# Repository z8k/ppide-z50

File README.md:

# ppide-z50
PPIDE card for Z50Bus

Heavily based on https://github.com/electrified/rc2014-82c55-ide

Intended for use with a horizontal-mounting 44-pin IDE Disk-On-Module module, this card omits the 40-pin IDE connector and external power input jack.

Notes:
1. Address selection is with the jumper pins in the lower right. Address bits A1 and A0 are ignored. Set to 0x20 (one jumper, on pin A5) for use with RomWBW and/or Fuzix.
2. You may wish to lower the value of R101 or use a super-bright LED if the disk activity light is a bit dim.

| Reference |  Value |
|-----------|--------|
| R101 | 470R resistor or lower value suitable for your LED |
| R102 | 10K resistor |
| R103 | 10K resistor |
| R104 | 10K resistor |
| C101 | 0.1uF ceramic capacitor |
| C102 | 0.1uF ceramic capacitor |
| C103 | 0.1uF ceramic capacitor |
| RN101 | 10K SIP resistor (8 pins, 7 resistors) |
| D101 | LED |
| U101 | 74HCT688 |
| U102 | 74HCT04 |
| U103 | 82C55A (PLCC package) |
| J101 | 2x25 2.54mm right-angle male box header |
| J102 | 2x8 2.54mm pitch right-angle pin header |
| J103 | 2x22 2mm pitch pin header |

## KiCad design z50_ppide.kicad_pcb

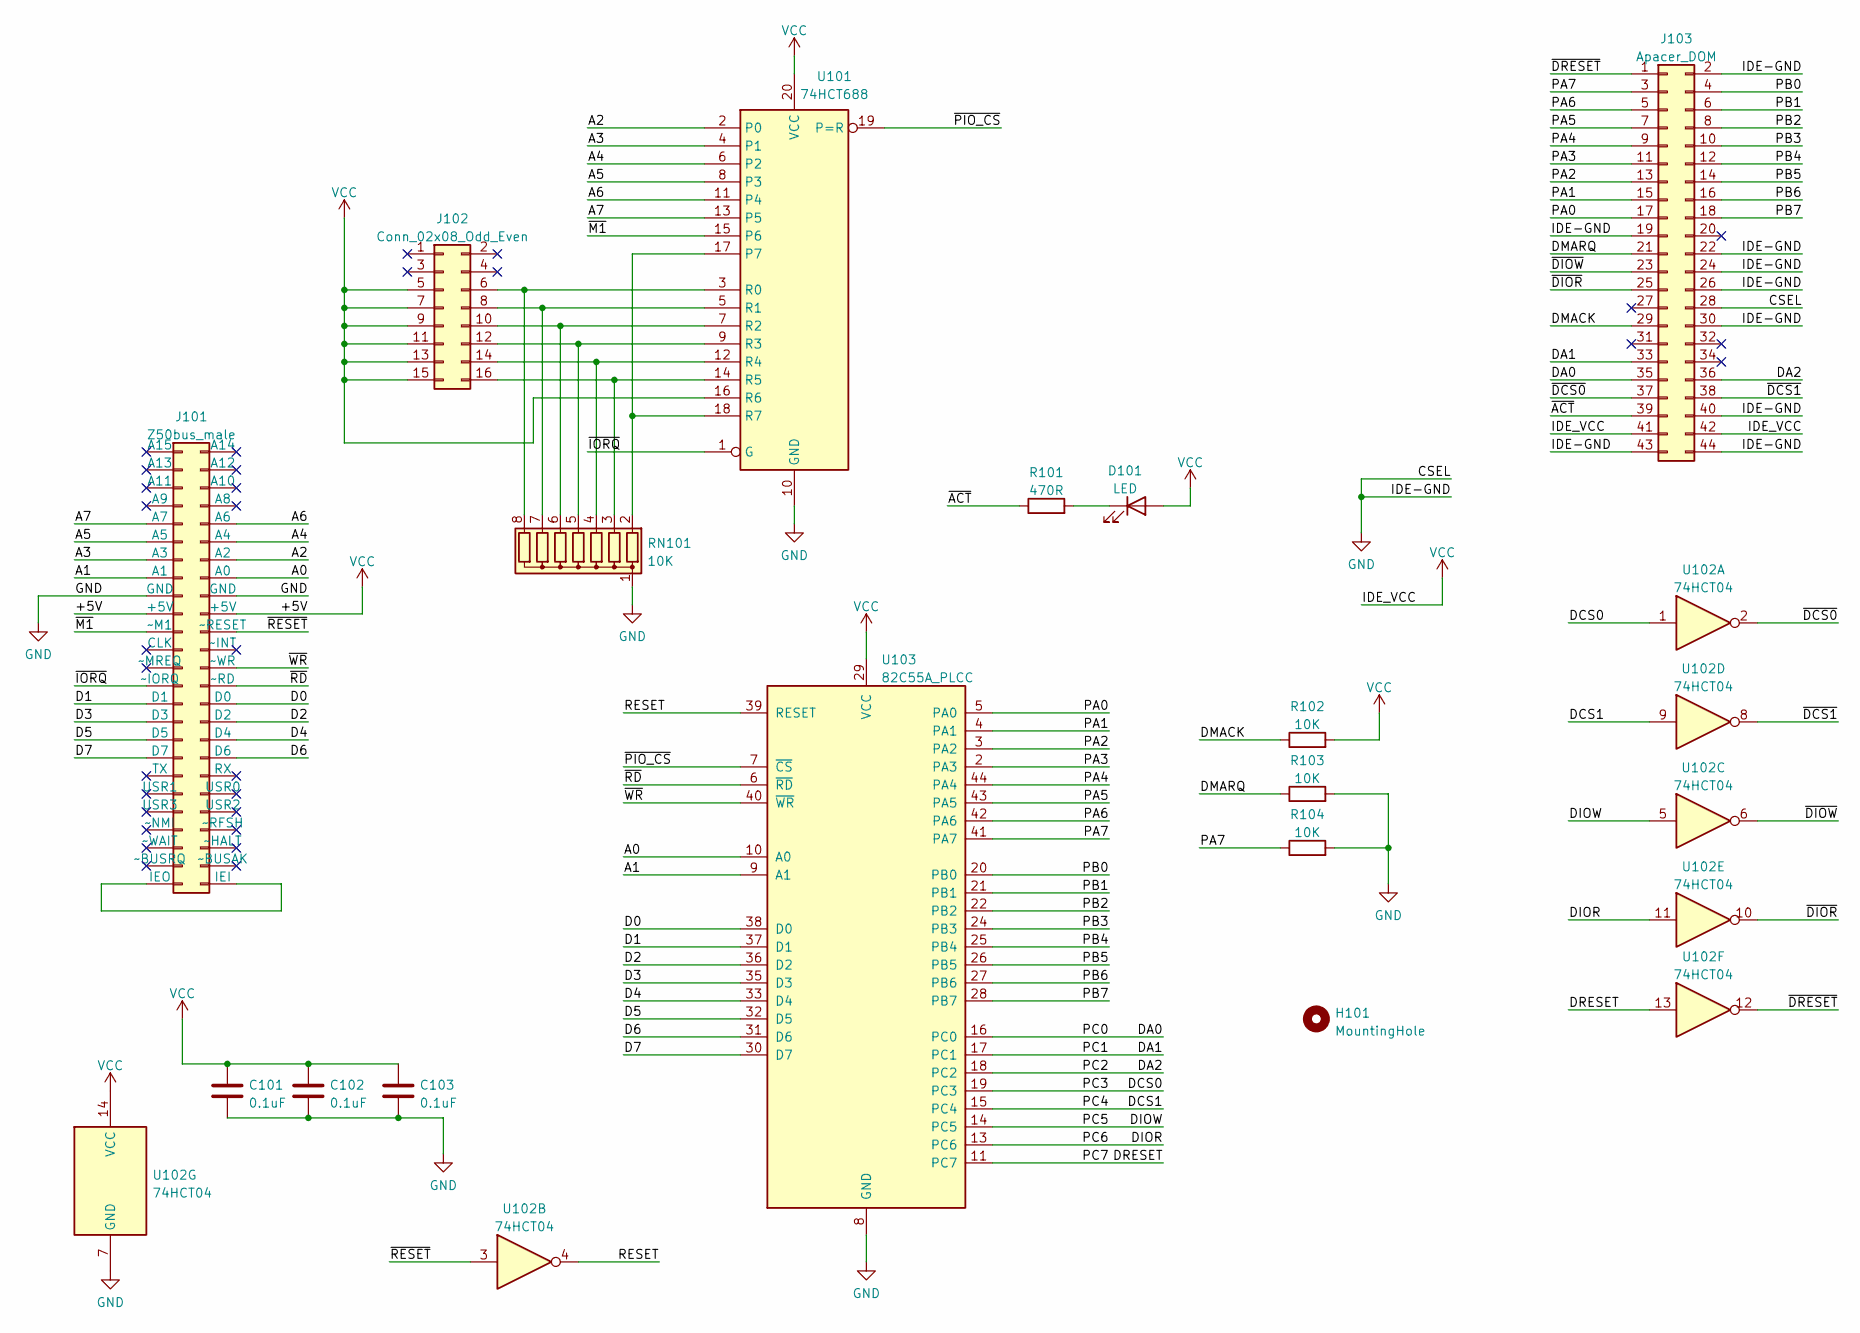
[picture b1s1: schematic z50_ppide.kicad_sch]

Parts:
C101, C102, C103: 0.1uF; C_Disc_D3.8mm_W2.6mm_P2.50mm
D101: LED; LED_D3.0mm
H101: MountingHole; MountingHole_3.2mm_M3_DIN965_Pad_TopBottom
J101: Z50bus_male; Z50bus module card edge
J102: Conn_02x08_Odd_Even; PinHeader_2x08_P2.54mm_Horizontal
J103: Apacer_DOM; Apacer DOM
R101: 470R; R_Axial_DIN0207_L6.3mm_D2.5mm_P10.16mm_Horizontal
R102, R103, R104: 10K; R_Axial_DIN0207_L6.3mm_D2.5mm_P10.16mm_Horizontal
RN101: 10K; R_Array_SIP8
U101: 74HCT688; DIP-20_W7.62mm_LongPads
U102: 74HCT04; DIP-14_W7.62mm_LongPads
U103: 82C55A_PLCC; PLCC-44_THT-Socket

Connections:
/A0: J101.16 (A0), U103.10 (A0)
/A1: J101.15 (A1), U103.9 (A1)
/A2: J101.14 (A2), U101.2 (P0)
/A3: J101.13 (A3), U101.4 (P1)
/A4: J101.12 (A4), U101.6 (P2)
/A5: J101.11 (A5), U101.8 (P3)
/A6: J101.10 (A6), U101.11 (P4)
/A7: J101.9 (A7), U101.13 (P5)
/D0: J101.30 (D0), U103.38 (D0)
/D1: J101.29 (D1), U103.37 (D1)
/D2: J101.32 (D2), U103.36 (D2)
/D3: J101.31 (D3), U103.35 (D3)
/D4: J101.34 (D4), U103.33 (D4)
/D5: J101.33 (D5), U103.32 (D5)
/D6: J101.36 (D6), U103.31 (D6)
/D7: J101.35 (D7), U103.30 (D7)
/DA0: J103.35, U103.16 (PC0)
/DA1: J103.33, U103.17 (PC1)
/DA2: J103.36, U103.18 (PC2)
/DCS0: U102.1, U103.19 (PC3)
/DCS1: U102.9, U103.15 (PC4)
/DIOR: U102.11, U103.13 (PC6)
/DIOW: U102.5, U103.14 (PC5)
/DMACK: J103.29, R102.1
/DMARQ: J103.21, R103.1
/DRESET: U102.13, U103.11 (PC7)
/PA0: J103.17, U103.5 (PA0)
/PA1: J103.15, U103.4 (PA1)
/PA2: J103.13, U103.3 (PA2)
/PA3: J103.11, U103.2 (PA3)
/PA4: J103.9, U103.44 (PA4)
/PA5: J103.7, U103.43 (PA5)
/PA6: J103.5, U103.42 (PA6)
/PA7: J103.3, R104.1, U103.41 (PA7)
/PB0: J103.4, U103.20 (PB0)
/PB1: J103.6, U103.21 (PB1)
/PB2: J103.8, U103.22 (PB2)
/PB3: J103.10, U103.24 (PB3)
/PB4: J103.12, U103.25 (PB4)
/PB5: J103.14, U103.26 (PB5)
/PB6: J103.16, U103.27 (PB6)
/PB7: J103.18, U103.28 (PB7)
/RESET: U102.4, U103.39 (RESET)
/~ACT: J103.39, R101.1
/~DCS0: J103.37, U102.2
/~DCS1: J103.38, U102.8
/~DIOR: J103.25, U102.10
/~DIOW: J103.23, U102.6
/~DRESET: J103.1, U102.12
/~IORQ: J101.27 (~IORQ), U101.1 (G)
/~M1: J101.21 (~M1), U101.15 (P6)
/~PIO_CS: U101.19 (P=R), U103.7 (~CS)
/~RD: J101.28 (~RD), U103.6 (~RD)
/~RESET: J101.22 (~RESET), U102.3
/~WR: J101.26 (~WR), U103.40 (~WR)
GND: C101.2, C102.2, C103.2, J101.17 (GND), J101.18 (GND), J103.2, J103.19, J103.22, J103.24, J103.26, J103.28, J103.30, J103.40, J103.43, J103.44, R103.2, R104.2, RN101.1 (common), U101.10 (GND), U102.7 (GND), U103.8 (GND)
unnamed: D101.1 (K), R101.2
unnamed: J101.49 (IEO), J101.50 (IEI)
unnamed: J102.6, RN101.8 (R7), U101.3 (R0)
unnamed: J102.8, RN101.7 (R6), U101.5 (R1)
unnamed: J102.10, RN101.6 (R5), U101.7 (R2)
unnamed: J102.12, RN101.5 (R4), U101.9 (R3)
unnamed: J102.14, RN101.4 (R3), U101.12 (R4)
unnamed: J102.16, RN101.3 (R2), U101.14 (R5)
unnamed: RN101.2 (R1), U101.17 (P7), U101.18 (R7)
VCC: C101.1, C102.1, C103.1, D101.2 (A), J101.19 (+5V), J101.20 (+5V), J102.5, J102.7, J102.9, J102.11, J102.13, J102.15, J103.41, J103.42, R102.2, U101.16 (R6), U101.20 (VCC), U102.14 (VCC), U103.29 (VCC)

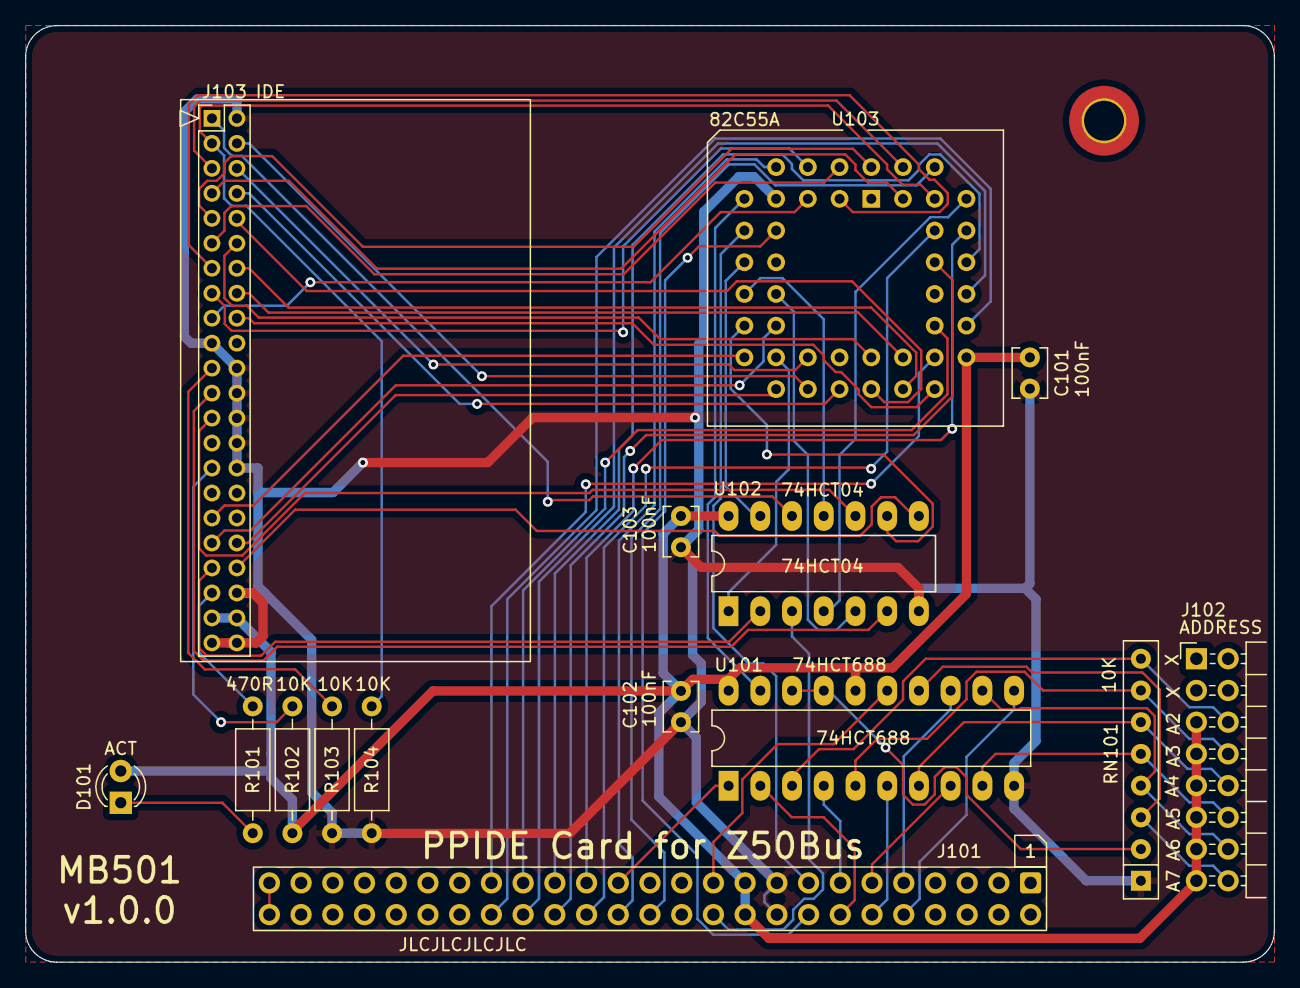
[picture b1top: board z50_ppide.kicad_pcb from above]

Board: 2 copper layers, 100.0 x 75.0 mm, 16 parts (0 on the bottom side), 66 nets.

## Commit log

2022-07-07 Add .gitignore
2022-07-07 V1.0.0 schematic and PCB layout
2022-07-07 V1.0.0 gerbers as sent to JLCPCB
2022-07-07 Remove extraneous file
2022-07-20 Add board image
2022-07-28 Add image of assembled card
